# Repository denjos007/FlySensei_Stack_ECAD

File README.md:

PCB design of stackable controllers for blimps

Each stack contains a specified function for controlling a blimp

# Stacks
Below is the description of each stack

## RPi Stack
This stack takes care of the vision system for the blimp. The hardware integrates a Raspberry Pi CM4 with a Google Coral Accelerator Module. This combination will connect to upto 3 external cameras and process the image information. The system can implement machine vision algorithms like YOLO to process the scene and extract relevent information. 

## Actuation Stack

## Realtime Stack

## Sensing Stack

## Communication Stack

# Contributors
Joseph Prince Mathew - jprincem@masonlive.gmu.edu

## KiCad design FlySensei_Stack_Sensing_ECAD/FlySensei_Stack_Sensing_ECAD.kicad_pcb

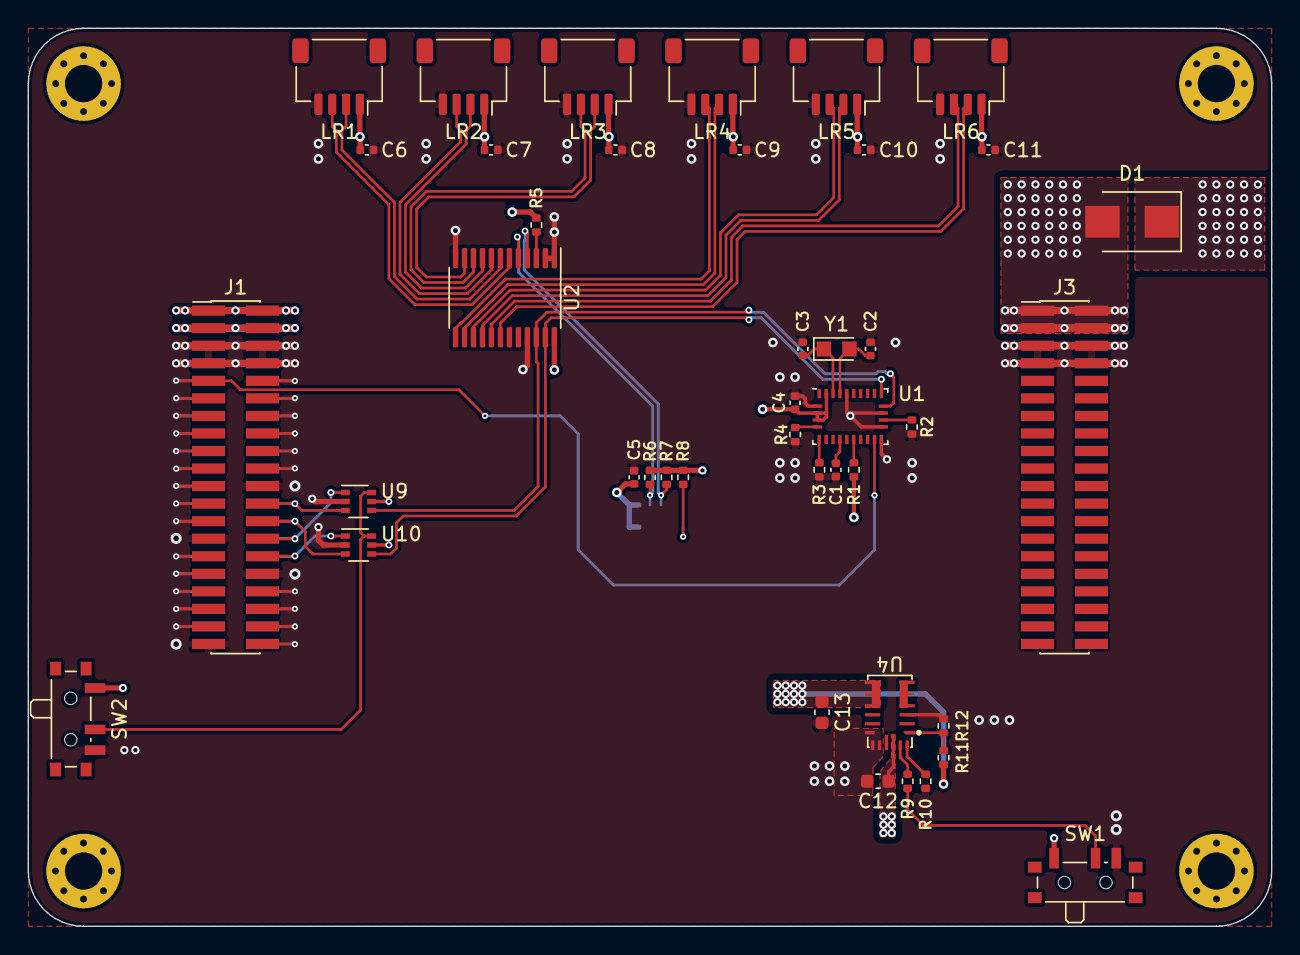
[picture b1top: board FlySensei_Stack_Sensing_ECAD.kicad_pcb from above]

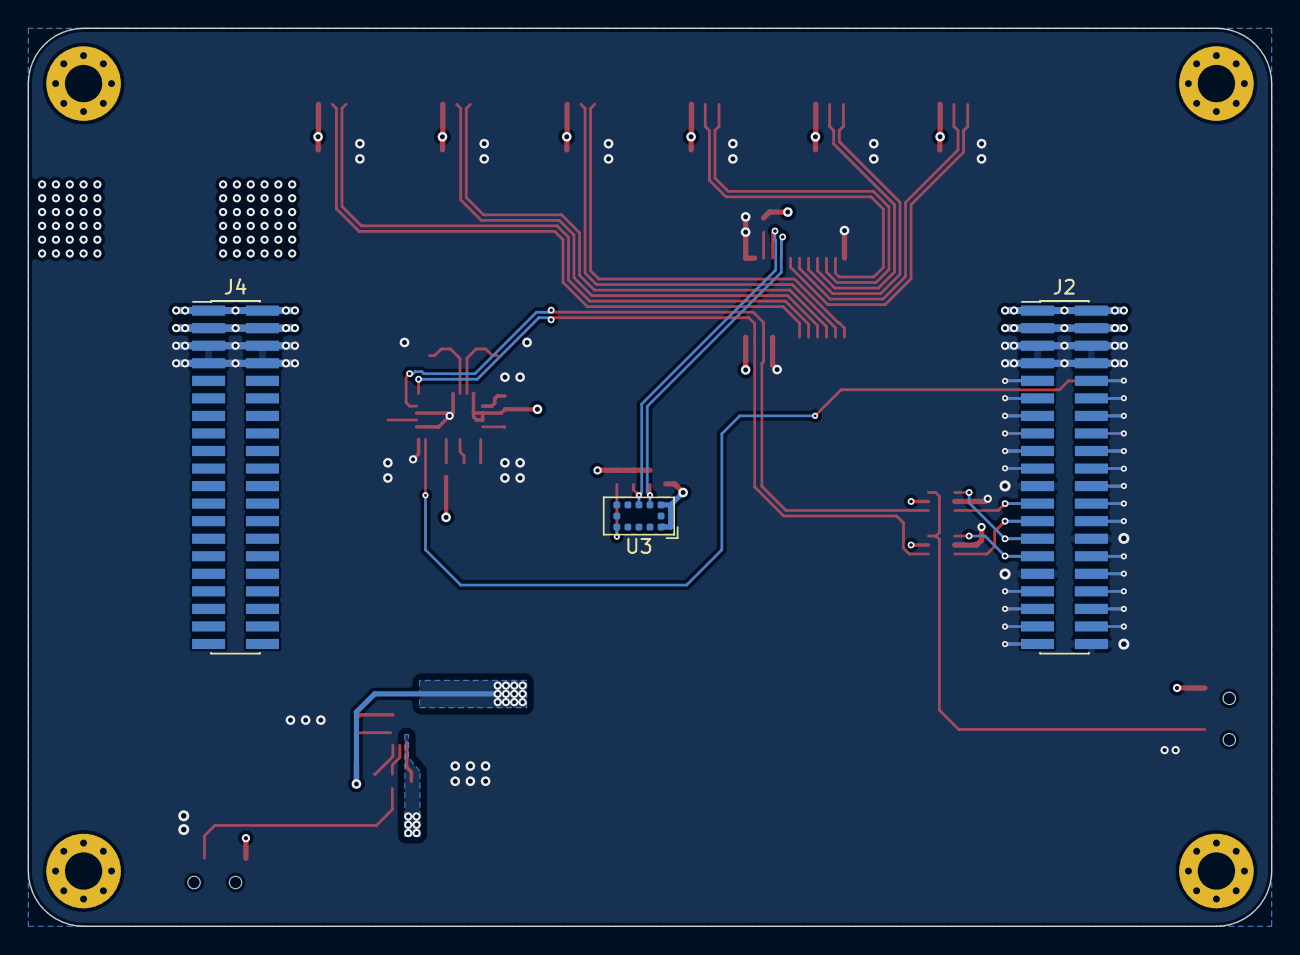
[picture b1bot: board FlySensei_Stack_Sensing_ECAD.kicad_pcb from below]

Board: 4 copper layers, 90.0 x 65.0 mm, 49 parts (3 on the bottom side), 62 nets.

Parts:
C1, C4, C5, C6, C7, C8, C9, C10, C11: 0u1F; C_0402_1005Metric
C2, C3: 22pF; C_0402_1005Metric
C12: 10uF; C_0603_1608Metric
C13: 22uF; C_0603_1608Metric
D1: D_SCHTKY; D_SMB
H1, H2, H3, H4: MountingHole; MountingHole_2.7mm_M2.5_Pad_Via
J1, J3: Conn_02x20_Odd_Even_Male; PinHeader_2x20_P1.27mm_Vertical_SMD
J2, J4: Conn_02x20_Odd_Even_Female; PinHeader_2x20_P1.27mm_Vertical_SMD
LR1, LR2, LR3, LR4, LR5, LR6: JST_SH_SM04; JST_SH_SM04B-SRSS-TB_1x04-1MP_P1.00mm_Horizontal
R1, R5: 0K; R_0402_1005Metric
R2, R3, R4, R6, R7, R8: 10K; R_0402_1005Metric
R9: 55K; R_0402_1005Metric
R10: 62K; R_0402_1005Metric
R11: 75K; R_0402_1005Metric
R12: 24K; R_0402_1005Metric
SW1, SW2: SW_SPDT; SW_SPDT_PCM12
U1: BNO055; LGA-28_5.2x3.8mm_P0.5mm
U2: TCA9548APWR; TSSOP-24_4.4x7.8mm_P0.65mm
U3: VL53L0CXV0DH_1; ST_VL53L1x
U4: MPM3610; MPM3610_QFN-20_5x3mm
U9, U10: TS5A3159ADCKR; SOT-363_SC-70-6
Y1: Crystal; Crystal_SMD_2012-2Pin_2.0x1.2mm_HandSoldering

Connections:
+3V3: C4.1, C5.1, C6.1, C7.1, C8.1, C9.1, C10.1, C11.1, C13.1, LR1.1, LR2.1, LR3.1, LR4.1, LR5.1, LR6.1, R1.1, R5.2, R6.1, R7.1, R8.1, R11.1, SW2.1 (A), U1.3 (VDD), U1.4 (~BOOT_LOAD_PIN), U1.28 (VDDIO), U2.24 (VCC), U3.1 (AVDDVCSEL), U3.11 (AVDD), U4.7 (OUT), U4.8 (OUT), U4.9 (OUT), U9.5 (V+), U10.5 (V+)
+BATT: C12.1, D1.1 (K), SW1.1 (A), U4.16 (IN)
/I2C Mux/I2C0.SCL: J1.24, J2.23, U9.3
/I2C Mux/I2C0.SDA: J1.26, J2.25, U10.3
/I2C Mux/I2C1.SCL: J1.28, J2.27, U9.1
/I2C Mux/I2C1.SDA: J1.30, J2.29, U10.1
/I2C Mux/I2C_SCL: U1.19 (COM1), U2.22 (SCL), U9.4
/I2C Mux/I2C_SDA: U1.20 (COM0), U2.23 (SDA), U10.4
/I2C Mux/I2C_SEL: SW2.2 (B), U9.6, U10.6
/LIDAR/I2C1_SCL: LR1.2, U2.7 (SC1)
/LIDAR/I2C1_SDA: LR1.3, U2.6 (SD1)
/LIDAR/I2C2_SCL: LR2.2, U2.9 (SC2)
/LIDAR/I2C2_SDA: LR2.3, U2.8 (SD2)
/LIDAR/I2C3_SCL: LR3.2, U2.11 (SC3)
/LIDAR/I2C3_SDA: LR3.3, U2.10 (SD3)
/LIDAR/I2C4_SCL: LR4.2, U2.14 (SC4)
/LIDAR/I2C4_SDA: LR4.3, U2.13 (SD4)
/LIDAR/I2C5_SCL: LR5.2, U2.16 (SC5)
/LIDAR/I2C5_SDA: LR5.3, U2.15 (SD5)
/LIDAR/I2C6_SCL: LR6.2, U2.18 (SC6)
/LIDAR/I2C6_SDA: LR6.3, U2.17 (SD6)
/PSU/3V3_EN: R9.1, SW1.2 (B)
/Stacking Connector/BATT_IN: D1.2 (A), J1.1, J1.2, J1.3, J1.4, J2.1, J2.2, J2.3, J2.4, J3.1, J3.2, J3.3, J3.4, J4.1, J4.2, J4.3, J4.4
/Stacking Connector/GPIO0: J1.9, J2.10, U1.14 (INT)
/Stacking Connector/GPIO1: J1.11, J2.12
/Stacking Connector/GPIO2: J1.10, J2.9
/Stacking Connector/GPIO3: J1.12, J2.11
/Stacking Connector/GPIO4: J1.14, J2.13
/Stacking Connector/GPIO5: J1.16, J2.15
/Stacking Connector/GPIO6: J1.18, J2.17
/Stacking Connector/GPIO7: J1.20, J2.19
/Stacking Connector/SPI0.CLK: J1.17, J2.18
/Stacking Connector/SPI0.CS0: J1.19, J2.20
/Stacking Connector/SPI0.CS1: J1.21, J2.22
/Stacking Connector/SPI0.CS2: J1.23, J2.24
/Stacking Connector/SPI0.CS3: J1.25, J2.26
/Stacking Connector/SPI0.MISO: J1.15, J2.16
/Stacking Connector/SPI0.MOSI: J1.13, J2.14
/Stacking Connector/SPI1.CLK: J1.33, J2.34
/Stacking Connector/SPI1.CS0: J1.35, J2.36
/Stacking Connector/SPI1.CS1: J1.37, J2.38
/Stacking Connector/SPI1.MISO: J1.31, J2.32
/Stacking Connector/SPI1.MOSI: J1.29, J2.30
/Stacking Connector/UART0.RX: J1.36, J2.35
/Stacking Connector/UART0.TX: J1.34, J2.33
/Stacking Connector/UART1.RX: J1.40, J2.39
/Stacking Connector/UART1.TX: J1.38, J2.37
GND: C1.1, C2.2, C3.2, C4.2, C5.2, C6.2, C7.2, C8.2, C9.2, C10.2, C11.2, C12.2, C13.2, J1.5, J1.6, J1.7, J1.8, J1.22, J1.27, J1.32, J1.39, J2.5, J2.6, J2.7, J2.8, J2.21, J2.28, J2.31, J2.40, J3.5, J3.6, J3.7, J3.8, J4.5, J4.6, J4.7, J4.8, LR1.4, LR2.4, LR3.4, LR4.4, LR5.4, LR6.4, R2.1, R3.2, R4.2, R10.2, R12.2, SW1.3 (C), SW2.3 (C), U1.2 (GND), U1.15 (GNDIO), U1.16 (GNDIO), U1.18 (COM2), U1.25 (GNDIO), U2.1 (A0), U2.2 (A1), U2.12 (GND), U2.21 (A2), U3.2 (AVSSVCSEL), U3.3 (GND), U3.4 (GND), U3.6 (GND), U3.12 (GND), U4.3 (AGND), U4.12 (PGND), U4.13 (PGND), U4.14 (PGND), U9.2 (GND), U10.2 (GND)
unnamed: C1.2, U1.9 (CAP)
unnamed: C2.1, U1.26 (XOUT32), Y1.2
unnamed: C3.1, U1.27 (XIN32), Y1.1
unnamed: R1.2, U1.11 (~RESET)
unnamed: R2.2, U1.17 (COM3)
unnamed: R3.1, U1.6 (PS0)
unnamed: R4.1, U1.5 (PS1)
unnamed: R5.1, U2.3 (~RESET)
unnamed: R6.2, U2.5 (SC0), U3.10 (SCL)
unnamed: R7.2, U2.4 (SD0), U3.9 (SDA)
unnamed: R8.2, U3.5 (XSHUT)
unnamed: R9.2, U4.17 (EN)
unnamed: R10.1, U4.18 (AAM)
unnamed: R11.2, R12.1, U4.1 (FB)

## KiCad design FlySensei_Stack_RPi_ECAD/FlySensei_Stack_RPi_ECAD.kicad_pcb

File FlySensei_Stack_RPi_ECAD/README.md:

Stackable base board for the Raspberry Pi CM4 with an integrated AI co-processor

# Functional Specifications
- Raspberry Pi CM4 used as the main processor
- Google Coral used as the AI co-processor
- Selectable Power input from USB-C port and Battery input from stack headers
- Ethernet and camera FFC ports

# Contributors
Joseph Prince Mathew - jprincem@masonlive.gmu.edu

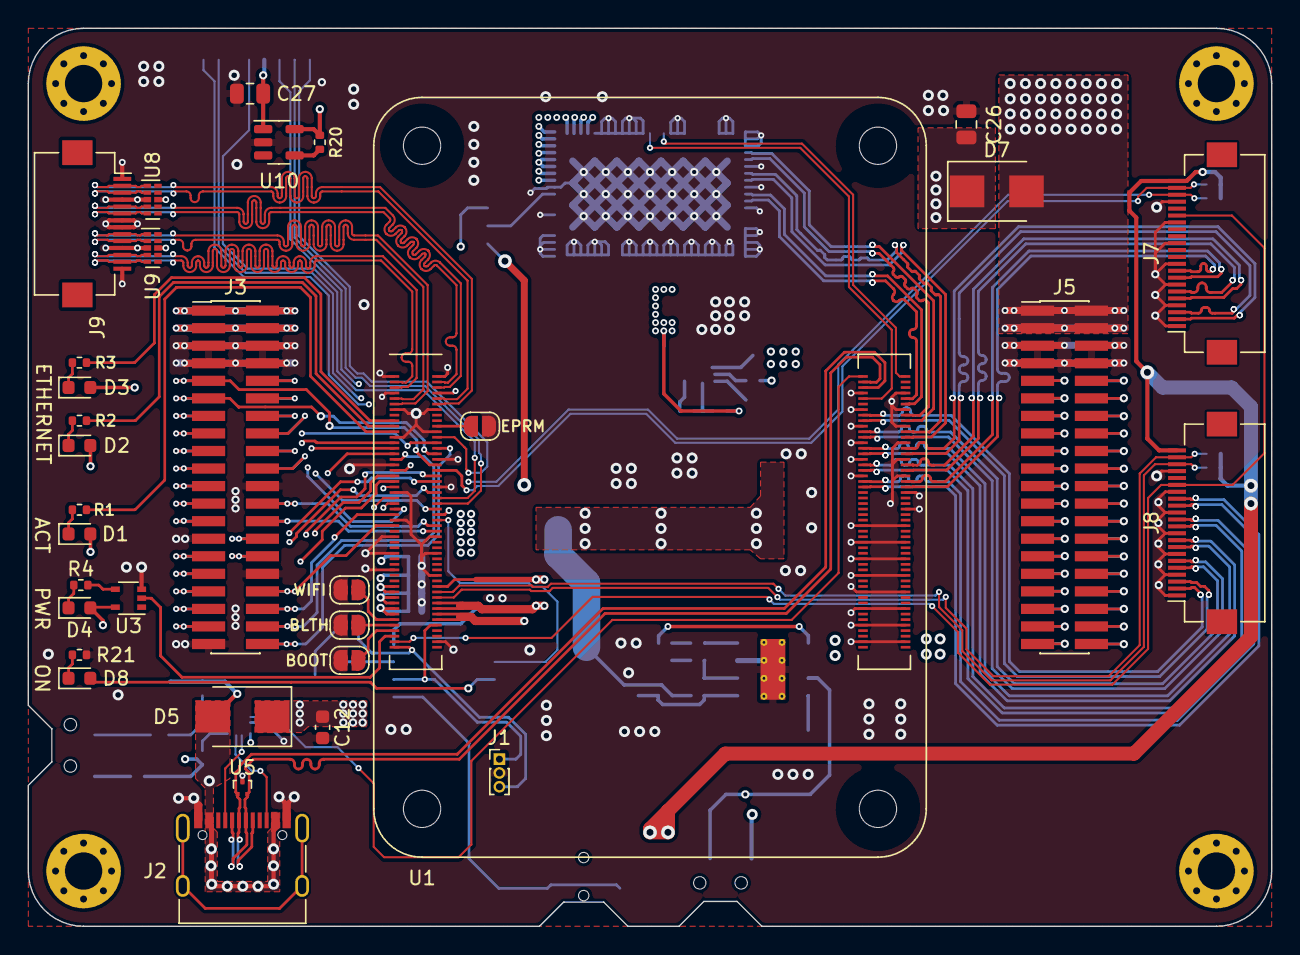
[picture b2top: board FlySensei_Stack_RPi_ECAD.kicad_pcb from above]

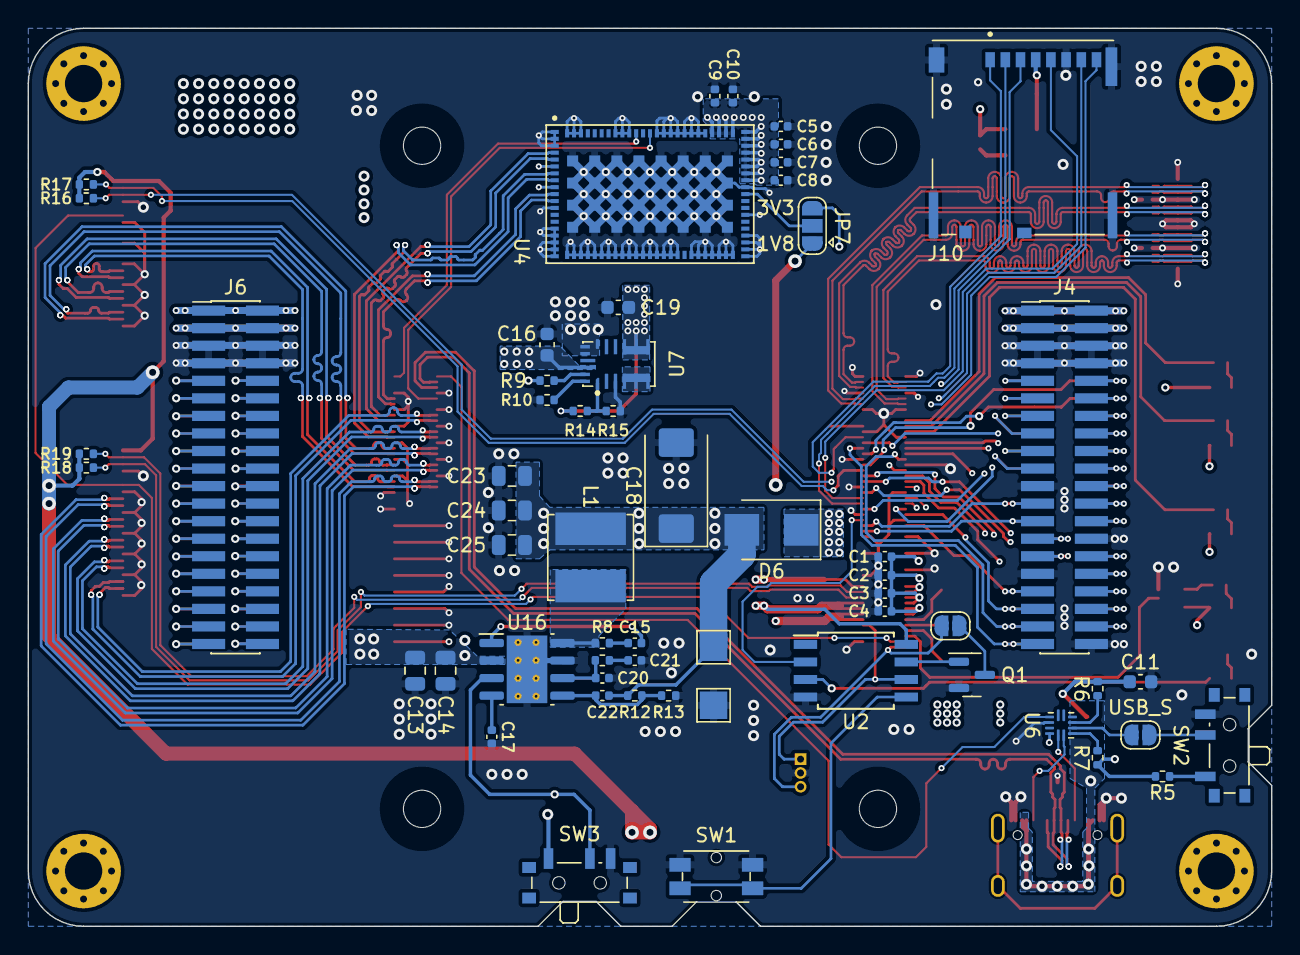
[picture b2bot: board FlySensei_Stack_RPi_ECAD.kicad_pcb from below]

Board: 4 copper layers, 90.0 x 65.0 mm, 95 parts (58 on the bottom side), 125 nets.

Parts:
C1, C2, C3, C4: 0u1 16V; C_0402_1005Metric
C5, C6, C7, C8, C9, C10: 0u1 6.3V; C_0402_1005Metric
C11, C19: 22u 16V; C_0603_1608Metric
C12: 1u 16V; C_0603_1608Metric
C13, C14: 10u 35v; C_0805_2012Metric
C15, C17: 100n 35V; C_0402_1005Metric
C16: 10u 35V; C_0603_1608Metric
C18: 100uF; CP_EIA-7343-31_Kemet-D
C20, C22: 1nf 16V; C_0402_1005Metric
C21: 1.2nF 16V; C_0402_1005Metric
C23, C24, C25: 22u 16V; C_0805_2012Metric
C26: 22u; C_0805_2012Metric
C27: 10u; C_0805_2012Metric
D1, D2: LED_GRN; LED_0603_1608Metric
D3: LED_AMB; LED_0603_1608Metric
D4: LED_RED; LED_0603_1608Metric
D5, D6, D7: D_Schottky; D_SMB
D8: LED_WHT; LED_0603_1608Metric
H1, H2, H3, H4: MountingHole; MountingHole_2.7mm_M2.5_Pad_Via
J1: Conn_01x03; PinHeader_1x03_P1.00mm_Vertical
J2: USB_C_Receptacle_USB2.0; USB_C_Receptacle_XKB_U262-16XN-4BVC11
J3, J5: Conn_02x20_Odd_Even_Male; PinHeader_2x20_P1.27mm_Vertical_SMD
J4, J6: Conn_02x20_Odd_Even_Female; PinHeader_2x20_P1.27mm_Vertical_SMD
J7, J8: Conn_01x22_Female; Hirose_FH12-22S-0.5SH_1x22-1MP_P0.50mm_Horizontal
J9: Conn_01x14_Female; Hirose_FH12-14S-0.5SH_1x14-1MP_P0.50mm_Horizontal
J10: Micro_SD_Card_Det; SDCARD_MOLEX_503398-1892
JP1, JP2, JP3, JP4, JP5, JP6: SolderJumper_2_Open; SolderJumper-2_P1.3mm_Open_RoundedPad1.0x1.5mm
JP7: SolderJumper_3_Open; SolderJumper-3_P1.3mm_Open_RoundedPad1.0x1.5mm
L1: SRN6045TA-3R3Y; L_Bourns_SRN6045TA
Q1: Q_NMOS_GSD; SOT-23
R1, R2, R3, R4: 270R; R_0402_1005Metric
R5: 4.7K; R_0402_1005Metric
R6: 900K; R_0402_1005Metric
R7: 50K; R_0402_1005Metric
R8: 10R; R_0402_1005Metric
R9: 55K; R_0402_1005Metric
R10: 62K; R_0402_1005Metric
R11: 20K 1%; R_0402_1005Metric
R12: 12K 1%; R_0402_1005Metric
R13: 2.2K 1%; R_0402_1005Metric
R14: 75K; R_0402_1005Metric
R15: 24K; R_0402_1005Metric
R16, R17, R18, R19: 10K; R_0402_1005Metric
R20: 12K; R_0402_1005Metric
R21: 480; R_0402_1005Metric
SW1: SW_SPST; Panasonic_EVQPUL_EVQPUC
SW2, SW3: SW_SPDT; SW_SPDT_PCM12
TP4, TP6: TestPoint; TestPoint_Pad_2.0x2.0mm
U1: ComputeModule4-CM4; Raspberry-Pi-4-Compute-Module
U2: ATtiny85V-10S; SOIC-8W_5.3x5.3mm_P1.27mm
U3: 74LVC1G07; SOT-353_SC-70-5
U4: G313-06329-00
U5: TPD2EUSB30; Texas_DRT-3
U6: TUSB321; Texas_X2QFN-12_1.6x1.6mm_P0.4mm
U7: MPM3610; MPM3610_QFN-20_5x3mm
U8, U9: TPD4EUSB30; USON-10_2.5x1.0mm_P0.5mm
U10: RT9742GGJ5; SOT-23-5
U16: AP64501SP-13; SOIC-8-1EP_3.9x4.9mm_P1.27mm_EP2.95x4.9mm_Mask2.71x3.4mm_Th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

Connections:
+1V8_RPI: JP7.1 (A), U1.88 (+1.8v_(Output)), U1.90 (+1.8v_(Output))
+3V3: C5.1, C6.1, C7.1, C8.1, C9.1, C10.1, C19.1, R14.1, U4.56 (VIN), U4.57 (VIN), U4.58 (VIN), U4.59 (VIN), U4.60 (VIN), U4.61 (VIN), U4.62 (VIN), U4.63 (VIN), U4.64 (VIN), U4.65 (VIN), U4.66 (VIN), U4.67 (VIN), U7.7 (OUT), U7.8 (OUT), U7.9 (OUT)
+3V3_RPI: D1.2 (A), D2.2 (A), D3.2 (A), D4.2 (A), J7.22, J8.22, JP7.3 (B), R16.1, R17.1, R18.1, R19.1, R20.1, U1.78 (GPIO_VREF(1.8v/3.3v_Input)), U1.84 (+3.3v_(Output)), U1.86 (+3.3v_(Output)), U2.8 (VCC), U3.5 (VCC), U10.5 (IN)
+5V: C1.1, C2.1, C3.1, C4.1, C12.1, D5.1 (K), D6.1 (K), R5.2, R7.1, U1.77 (+5v_(Input)), U1.79 (+5v_(Input)), U1.81 (+5v_(Input)), U1.83 (+5v_(Input)), U1.85 (+5v_(Input)), U1.87 (+5v_(Input)), U6.12 (VDD)
+BATT: C13.1, C14.1, C16.1, C26.1, D7.1 (K), SW3.1 (A), U7.16 (IN), U16.2 (VIN)
/AI/CORL_PCIE_CLK_N: U1.112 (PCIe_CLK_N), U4.10 (PCIE_REFCLK_N)
/AI/CORL_PCIE_CLK_P: U1.110 (PCIe_CLK_P), U4.11 (PCIE_REFCLK_P)
/AI/CORL_PCIE_NCLKREQ: U1.102 (PCIe_CLK_nREQ), U4.78 (CLKREQ)
/AI/CORL_PCIE_NRST: U1.109 (PCIe_nRST), U4.76 (RST)
/AI/CORL_PCIE_RX_N: U1.124 (PCIe_TX_N), U4.8 (PCIE_RX_N)
/AI/CORL_PCIE_RX_P: U1.122 (PCIe_TX_P), U4.7 (PCIE_RX_P)
/AI/CORL_PCIE_TX_N: U1.118 (PCIe_RX_N), U4.4 (PCIE_TX_N)
/AI/CORL_PCIE_TX_P: U1.116 (PCIe_RX_P), U4.5 (PCIE_TX_P)
/High Speed Interfaces/CAM0_MIPI.C_N: J7.8, U1.140 (CAM0_C_N)
/High Speed Interfaces/CAM0_MIPI.C_P: J7.9, U1.142 (CAM0_C_P)
/High Speed Interfaces/CAM0_MIPI.D0_N: J7.2, U1.128 (CAM0_D0_N)
/High Speed Interfaces/CAM0_MIPI.D0_P: J7.3, U1.130 (CAM0_D0_P)
/High Speed Interfaces/CAM0_MIPI.D1_N: J7.5, U1.134 (CAM0_D1_N)
/High Speed Interfaces/CAM0_MIPI.D1_P: J7.6, U1.136 (CAM0_D1_P)
/High Speed Interfaces/CAM0_SCL: J7.20, R16.2, U1.35 (ID_SC)
/High Speed Interfaces/CAM0_SDA: J7.21, R17.2, U1.36 (ID_SD)
/High Speed Interfaces/CAM1_MIPI.C_N: J8.8, U1.127 (CAM1_C_N)
/High Speed Interfaces/CAM1_MIPI.C_P: J8.9, U1.129 (CAM1_C_P)
/High Speed Interfaces/CAM1_MIPI.D0_N: J8.2, U1.115 (CAM1_D0_N)
/High Speed Interfaces/CAM1_MIPI.D0_P: J8.3, U1.117 (CAM1_D0_P)
/High Speed Interfaces/CAM1_MIPI.D1_N: J8.5, U1.121 (CAM1_D1_N)
/High Speed Interfaces/CAM1_MIPI.D1_P: J8.6, U1.123 (CAM1_D1_P)
/High Speed Interfaces/CAM1_MIPI.D2_N: J8.11, U1.133 (CAM1_D2_N)
/High Speed Interfaces/CAM1_MIPI.D2_P: J8.12, U1.135 (CAM1_D2_P)
/High Speed Interfaces/CAM1_MIPI.D3_N: J8.14, U1.139 (CAM1_D3_N)
/High Speed Interfaces/CAM1_MIPI.D3_P: J8.15, U1.141 (CAM1_D3_P)
/High Speed Interfaces/CAM1_SCL: J8.20, R18.2, U1.80 (SCL0)
/High Speed Interfaces/CAM1_SDA: J8.21, R19.2, U1.82 (SDA0)
/High Speed Interfaces/CAM_GPIO: J7.17, J8.17, U1.97 (Camera_GPIO)
/High Speed Interfaces/ETH.0_N: J9.3, U1.10 (Ethernet_Pair0_N), U8.2 (D1-)
/High Speed Interfaces/ETH.0_P: J9.2, U1.12 (Ethernet_Pair0_P), U8.1 (D1+)
/High Speed Interfaces/ETH.1_N: J9.6, U1.4 (Ethernet_Pair1_P), U8.5 (D2-)
/High Speed Interfaces/ETH.1_P: J9.5, U1.6 (Ethernet_Pair1_N), U8.4 (D2+)
/High Speed Interfaces/ETH.2_N: J9.10, U1.9 (Ethernet_Pair2_N), U9.2 (D1-)
/High Speed Interfaces/ETH.2_P: J9.9, U1.11 (Ethernet_Pair2_P), U9.1 (D1+)
/High Speed Interfaces/ETH.3_N: J9.13, U1.3 (Ethernet_Pair3_P), U9.5 (D2-)
/High Speed Interfaces/ETH.3_P: J9.12, U1.5 (Ethernet_Pair3_N), U9.4 (D2+)
/PSU/PSU_EN: R9.1, SW3.2 (B), U16.3 (EN)
/RPi_CM4/ETH_nLED1: R2.2, U1.19 (Ethernet_nLED1(3.3v))
/RPi_CM4/ETH_nLED2: R3.2, U1.17 (Ethernet_nLED2(3.3v))
/RPi_CM4/GPIO_0: J3.9, J4.10, U1.34 (GPIO5)
/RPi_CM4/GPIO_1: J3.11, J4.12, U1.30 (GPIO6)
/RPi_CM4/GPIO_2: J3.10, J4.9
/RPi_CM4/GPIO_3: J3.12, J4.11
/RPi_CM4/GPIO_4: J3.14, J4.13
/RPi_CM4/GPIO_5: J3.16, J4.15
/RPi_CM4/GPIO_6: J3.18, J4.17
/RPi_CM4/GPIO_7: J3.20, J4.19
/RPi_CM4/I2C0.SCL: J3.24, J4.23, U1.56 (GPIO3)
/RPi_CM4/I2C0.SDA: J3.26, J4.25, U1.58 (GPIO2)
/RPi_CM4/RPI_GLOBL_EN: J1.3, JP5.2 (B), U1.99 (Global_EN)
/RPi_CM4/RPI_RUN_PG: J1.1, U1.92 (RUN_PG), U2.6 (PB1)
/RPi_CM4/RPI_SHTDWN: U1.54 (GPIO4), U2.2 (XTAL1/PB3)
/RPi_CM4/RPI_nLED_ACT: R1.2, U1.21 (PI_nLED_Activity)
/RPi_CM4/RPI_nLED_PWR: U1.95 (PI_nLED_PWR), U3.2
/RPi_CM4/SD_D_CLK: J10.5 (CLK), U1.46 (GPIO22)
/RPi_CM4/SD_D_CMD: J10.3 (CMD), U1.47 (GPIO23)
/RPi_CM4/SD_D_DAT0: J10.7 (DAT0), U1.45 (GPIO24)
/RPi_CM4/SD_D_DAT1: J10.8 (DAT1), U1.41 (GPIO25)
/RPi_CM4/SD_D_DAT2: J10.1 (DAT2), U1.24 (GPIO26)
/RPi_CM4/SD_D_DAT3: J10.2 (DAT3/CD), U1.48 (GPIO27)
/RPi_CM4/SPI0.CLK: J3.17, J4.18, U1.25 (GPIO21)
/RPi_CM4/SPI0.CS0: J3.19, J4.20, U1.49 (GPIO18)
/RPi_CM4/SPI0.CS1: J3.21, J4.22, U1.50 (GPIO17)
/RPi_CM4/SPI0.CS2: J3.23, J4.24, U1.29 (GPIO16)
/RPi_CM4/SPI0.CS3: J3.25, J4.26
/RPi_CM4/SPI0.MISO: J3.15, J4.16, U1.26 (GPIO19)
/RPi_CM4/SPI0.MOSI: J3.13, J4.14, U1.27 (GPIO20)
/RPi_CM4/SPI1.CLK: J3.33, J4.34, U1.38 (GPIO11)
/RPi_CM4/SPI1.CS0: J3.35, J4.36, U1.39 (GPIO8)
/RPi_CM4/SPI1.CS1: J3.37, J4.38, U1.37 (GPIO7)
/RPi_CM4/SPI1.MISO: J3.31, J4.32, U1.40 (GPIO9)
/RPi_CM4/SPI1.MOSI: J3.29, J4.30, U1.44 (GPIO10)
/RPi_CM4/UART0.RX: J3.36, J4.35, U1.51 (GPIO15)
/RPi_CM4/UART0.TX: J3.34, J4.33, U1.55 (GPIO14)
/RPi_CM4/UART1.RX: J3.40, J4.39, U1.28 (GPIO13)
/RPi_CM4/UART1.TX: J3.38, J4.37, U1.31 (GPIO12)
/RPi_CM4/USB_DN: J2.A7 (D-), J2.B7 (D-), U1.103 (USB2_N), U5.2 (D-)
/RPi_CM4/USB_DP: J2.A6 (D+), J2.B6 (D+), U1.105 (USB2_P), U5.1 (D+)
/RPi_CM4/USB_ID: U1.101 (USB_OTG_ID), U6.9 (ID)
/SD Card/SD_PWR: C27.1, J10.4 (VDD), U10.1 (OUT)
/Stacking Connectors/BATT_IN: D7.2 (A), J3.1, J3.2, J3.3, J3.4, J4.1, J4.2, J4.3, J4.4, J5.1, J5.2, J5.3, J5.4, J6.1, J6.2, J6.3, J6.4
/Stacking Connectors/I2C1.SCL: J3.28, J4.27
/Stacking Connectors/I2C1.SDA: J3.30, J4.29
GND: C1.2, C2.2, C3.2, C4.2, C5.2, C6.2, C7.2, C8.2, C9.2, C10.2, C11.2, C12.2, C13.2, C14.2, C16.2, C17.2, C18.2, C19.2, C20.2, C21.2, C23.2, C24.2, C25.2, C26.2, C27.2, J1.2, J2.A1 (GND), J2.A12 (GND), J2.B1 (GND), J2.B12 (GND), J3.5, J3.6, J3.7, J3.8, J3.22, J3.27, J3.32, J3.39, J4.5, J4.6, J4.7, J4.8, J4.21, J4.28, J4.31, J4.40, J5.5, J5.6, J5.7, J5.8, J6.5, J6.6, J6.7, J6.8, J7.1, J7.4, J7.7, J7.10, J7.13, J7.16, J7.19, J8.1, J8.4, J8.7, J8.10, J8.13, J8.16, J8.19, J9.1, J9.4, J9.7, J9.8, J9.11, J9.14, J10.6 (VSS), J10.11 (SHIELD), JP1.1 (A), JP2.1 (A), JP3.1 (A), JP4.1 (A), Q1.2 (S), R10.2, R13.2, R15.2, R21.2, SW1.2 (B), SW2.3 (C), SW3.3 (C), TP6.1, U1.1 (GND), U1.2 (GND), U1.7 (GND), U1.8 (GND), U1.13 (GND), U1.14 (GND), U1.22 (GND), U1.23 (GND), U1.32 (GND), U1.33 (GND), U1.42 (GND), U1.43 (GND), U1.52 (GND), U1.53 (GND), U1.59 (GND), U1.60 (GND), U1.65 (GND), U1.66 (GND), U1.71 (GND), U1.74 (GND), U1.98 (GND), U1.107 (GND), U1.108 (GND), U1.113 (GND), U1.114 (GND), U1.119 (GND), U1.120 (GND), U1.125 (GND), U1.126 (GND), U1.131 (GND), U1.132 (GND), U1.137 (GND), U1.138 (GND), U1.144 (GND), U1.150 (GND), U1.155 (GND), U1.156 (GND), U1.161 (GND), U1.162 (GND), U1.167 (GND), U1.168 (GND), U1.173 (GND), U1.174 (GND), U1.179 (GND), U1.180 (GND), U1.185 (GND), U1.186 (GND), U1.191 (GND), U1.192 (GND), U1.197 (GND), U1.198 (GND), U2.4 (GND), U3.3 (GND), U4.1 (GND), U4.2 (GND), U4.3 (GND), U4.6 (GND), U4.9 (GND), U4.12 (GND), U4.15 (GND), U4.16 (GND), U4.17 (GND), U4.18 (GND), U4.19 (GND), U4.20 (GND), U4.21 (GND), U4.22 (GND), U4.23 (GND), U4.24 (GND), U4.25 (GND), U4.26 (GND), U4.27 (GND), U4.28 (GND), U4.29 (GND), U4.30 (GND), U4.31 (GND), U4.32 (GND), U4.33 (GND), U4.34 (GND), U4.35 (GND), U4.36 (GND), U4.38 (GND), U4.39 (GND), U4.40 (GND), U4.41 (GND), U4.42 (GND), U4.43 (GND), U4.44 (GND), U4.45 (GND), U4.46 (GND), U4.47 (GND), U4.48 (GND), U4.51 (GND), U4.55 (GND), U4.68 (GND), U4.69 (GND), U4.70 (GND), U4.71 (GND), U4.72 (GND), U4.73 (GND), U4.74 (GND), U4.75 (GND), U4.79 (GND), U4.80 (GND), U4.81 (GND), U4.86 (GND), U4.87 (GND), U4.88 (GND), U4.89 (GND), U4.90 (GND), U4.91 (GND), U4.92 (GND), U4.93 (GND), U4.94 (GND), U4.95 (GND), U4.96 (GND), U4.97 (GND), U4.98 (GND), U4.99 (GND), U4.100 (GND), U4.101 (GND), U4.102 (GND), U4.103 (GND), U4.104 (GND), U4.105 (GND), U4.106 (GND), U4.107 (GND), U4.108 (GND), U4.109 (GND), U4.110 (GND), U4.111 (GND), U4.112 (GND), U4.113 (GND), U4.114 (GND), U4.115 (GND), U4.116 (GND), U4.117 (GND), U4.118 (GND), U4.119 (GND), U4.120 (GND), U5.3 (GND), U6.10 (GND), U7.3 (AGND), U7.12 (PGND), U7.13 (PGND), U7.14 (PGND), U8.3 (GND), U8.8 (GND), U9.3 (GND), U9.8 (GND), U10.2 (GND), U16.7 (GND), U16.9 (EP)
unnamed: C11.1, D5.2 (A), J2.A4 (VBUS), J2.A9 (VBUS), J2.B4 (VBUS), J2.B9 (VBUS), R6.2
unnamed: C15.1, R8.2
unnamed: C15.2, U16.1 (BST)
unnamed: C17.1, U16.4 (SS)
unnamed: C18.1, C22.1, C23.1, C24.1, C25.1, D6.2 (A), L1.2, R12.1, TP4.1
unnamed: C20.1, R11.1, U16.6 (COMP)
unnamed: C21.1, R11.2
unnamed: C22.2, R12.2, R13.1, U16.5 (FB)
unnamed: D1.1 (K), R1.1
unnamed: D2.1 (K), R2.1
unnamed: D3.1 (K), R3.1
unnamed: D4.1 (K), R4.1
unnamed: D8.1 (K), R21.1
unnamed: D8.2 (A), U2.3 (XTAL2/PB4)
unnamed: J2.A5 (CC1), U6.1 (CC1)
unnamed: J2.B5 (CC2), U6.2 (CC2)
unnamed: JP1.2 (B), U1.93 (nRPIBOOT)
unnamed: JP2.2 (B), U1.20 (EEPROM_nWP)
unnamed: JP3.2 (B), U1.89 (WiFi_nDisable)
unnamed: JP4.2 (B), U1.91 (BT_nDisable)
unnamed: JP5.1 (A), Q1.3 (D)
unnamed: JP6.1 (A), SW2.2 (B)
unnamed: JP6.2 (B), U6.4 (PORT)
unnamed: JP7.2 (C), U4.54 (AON)
unnamed: L1.1, R8.1, U16.8 (SW)
unnamed: Q1.1 (G), U2.7 (PB2)
unnamed: R4.2, U3.4
unnamed: R5.1, SW2.1 (A)
unnamed: R6.1, U6.5 (VBUS_DET)
unnamed: R7.2, U6.3 (CURRENT_MODE)
unnamed: R9.2, U7.17 (EN)
unnamed: R10.1, U7.18 (AAM)
unnamed: R14.2, R15.1, U7.1 (FB)
unnamed: R20.2, U10.4 (EN)
unnamed: SW1.1 (A), U2.5 (AREF/PB0)

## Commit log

2021-05-26 Completed Schematic
2021-06-02 PCB Design for the Raspberry PI CM4 Board (V0.1)
2021-06-07 Add PCB design for the actuation board
2021-06-07 Change name of stacking connector schematic file in RPI Stack
2021-06-07 Create Template for the Stacking board
2021-06-07 Add .gitignore
2021-06-09 Add PCB fabrication files
2021-06-09 Cleanup component values to remain consistent in all skeets
2021-06-09 Add Readme.md for all projects
2021-06-09 Update part number for fuel gauge IC
2021-06-09 remove report
2021-06-15 Rename PCBWay BOM as general BOM
2021-06-15 Create IMXRT1170 board Design files
2021-06-16 Change PWM generation IC package to TSSOP due to availibility
2021-06-16 Add backup of IMXRT1176 to gitignore
2021-06-23 PCB Design Added for Sensing Stack
